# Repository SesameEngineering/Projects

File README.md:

# Projects
Current Sesame Projects

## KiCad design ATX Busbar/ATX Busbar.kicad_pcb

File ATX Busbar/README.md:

This project is a small PCb on which you plug a standard ATX PSU.

You can use it to power up OCP servers plugging it directly on the servers (Leopard V2, Tioga Pass and Yosemite V1) or using the busbar (Leopard V1, Bryce Canyon, Big Sur).

It can power up to 1kW.

It is also compatible with OCP Medusa cable to power up 3 servers at the same time.

On onboard LED indicates if power is on or not

Be careful when it is plugged not to touch directly the busbars. A plastic cover is used for safety

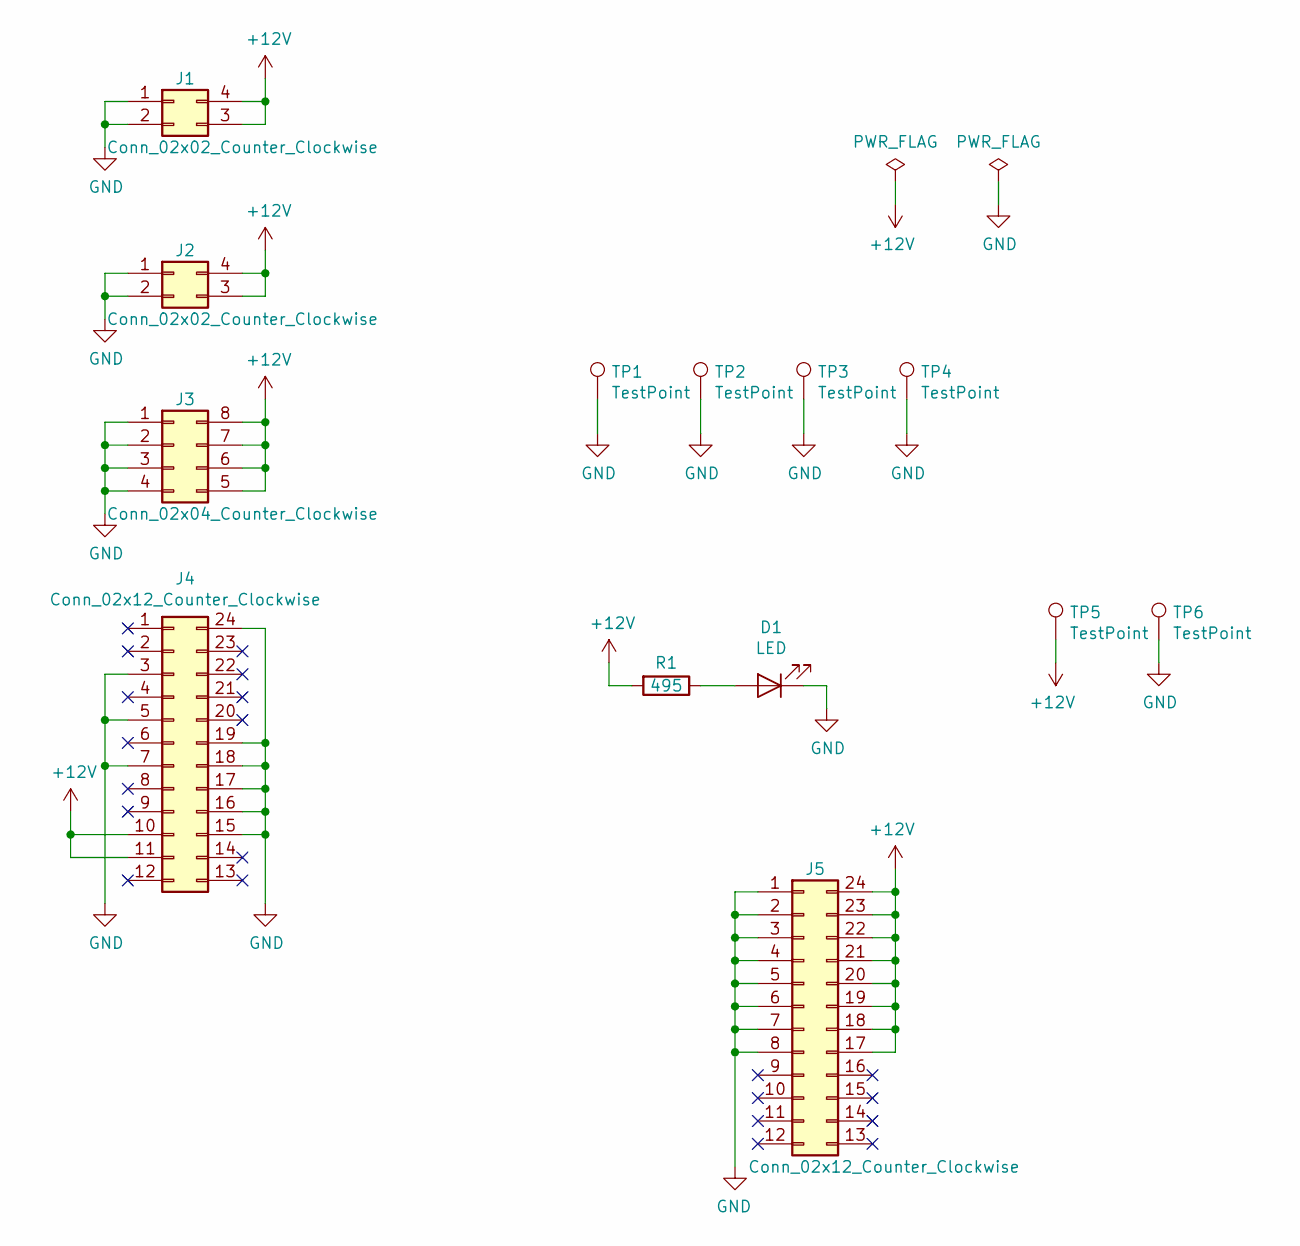
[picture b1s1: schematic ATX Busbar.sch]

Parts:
D1: LED; LED_1206
J1, J2: Conn_02x02_Counter_Clockwise; 2x2pins_2.38mm_0462070104
J3: Conn_02x04_Counter_Clockwise; 2x4pins_2.38mm_13A_0462070108
J4: Conn_02x12_Counter_Clockwise; Connector_2x12_2.5mm_thickness
J5: Conn_02x12_Counter_Clockwise; 2-6450880-8
R1: 495; R_1206
TP1, TP2, TP3, TP4: TestPoint; fixing_hole
TP5, TP6: TestPoint; pad_busbar

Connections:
+12V: J1.3, J1.4, J2.3, J2.4, J3.5, J3.6, J3.7, J3.8, J4.10, J4.11, J5.17, J5.18, J5.19, J5.20, J5.21, J5.22, J5.23, J5.24, R1.2, TP5.1
GND: D1.1 (K), J1.1, J1.2, J2.1, J2.2, J3.1, J3.2, J3.3, J3.4, J4.3, J4.5, J4.7, J4.15, J4.16, J4.17, J4.18, J4.19, J4.24, J5.1, J5.2, J5.3, J5.4, J5.5, J5.6, J5.7, J5.8, TP1.1, TP2.1, TP3.1, TP4.1, TP6.1
unnamed: D1.2 (A), R1.1

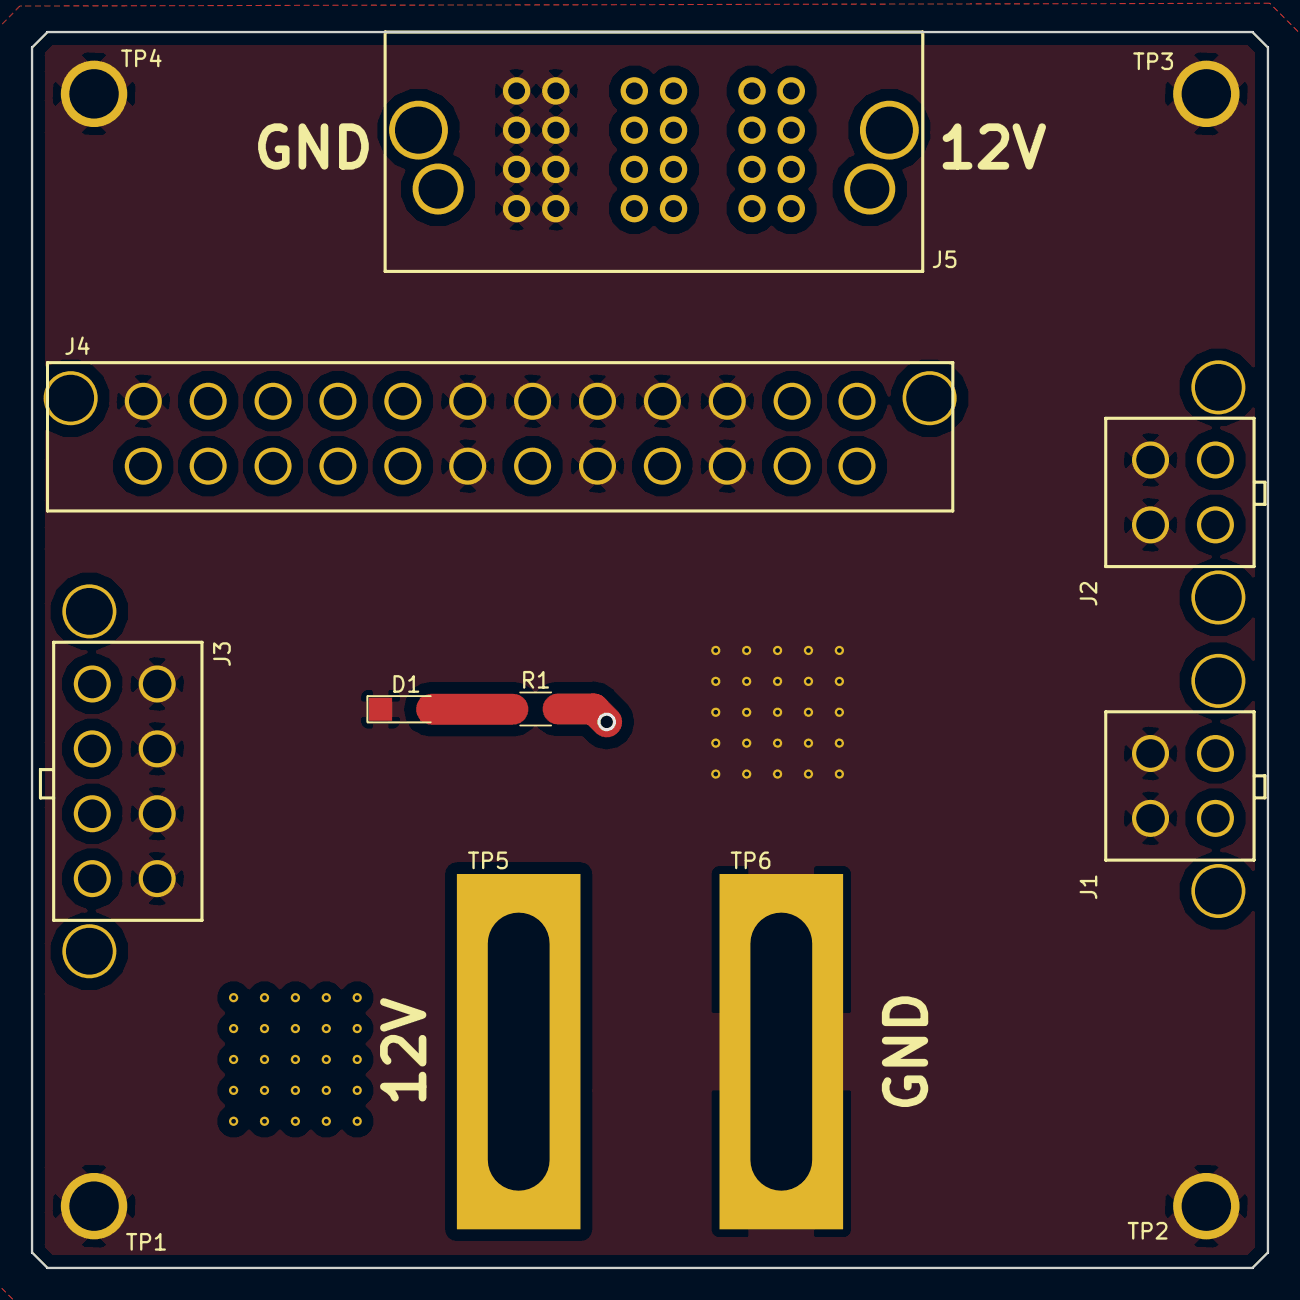
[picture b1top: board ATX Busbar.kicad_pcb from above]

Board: 2 copper layers, 80.0 x 80.0 mm, 13 parts (0 on the bottom side), 3 nets.

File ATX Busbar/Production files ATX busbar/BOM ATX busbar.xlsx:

Id | Reference | Footprint | Quantity | Designation | Manufacturer part number | Supplier part number | Manufacturer | Unit price | Total price | Comment
2 | D1 | LED_1206 | 1 | LED | 599-0260-007F | 645-599-0260-007F | Dialight | 0.34899999999999998 | 0.34899999999999998
3 | J1,J2 | power_SSD_2x2pins | 2 | Conn_02x02_Counter_Clockwise | 462070104 | WM20237-ND | Molex | 2.1800000000000002 | 4.3600000000000003
4 | J3 | proc_2x4pins | 1 | Conn_02x04_Counter_Clockwise | 462070108 | WM23313-ND | Molex | 2.62 | 2.62
5 | J4 | atx2x12pins | 1 | Conn_02x12_Counter_Clockwise | 46207-0124 | 538-46207-0124 | Molex | 5.67 | 5.67
6 | R1 | R_1206 | 1 | 495 | RT1206DRE07493RL | 603-RT1206DRE07493RL | Yageo | 0.46300000000000002 | 0.46300000000000002
7 | J5 | 2-6450880-8 | 1 | Conn_02x12_Counter_Clockwise |  |  |  |  |  | Pressfit - Provided by ITRenew - To assemble
 |  |  |  |  |  |  |  |  | 13.462

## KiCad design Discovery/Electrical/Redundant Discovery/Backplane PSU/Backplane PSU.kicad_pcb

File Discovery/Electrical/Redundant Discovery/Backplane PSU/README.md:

Design files and production files for the Backplane PSU (PCB on which you plug the PSUs)

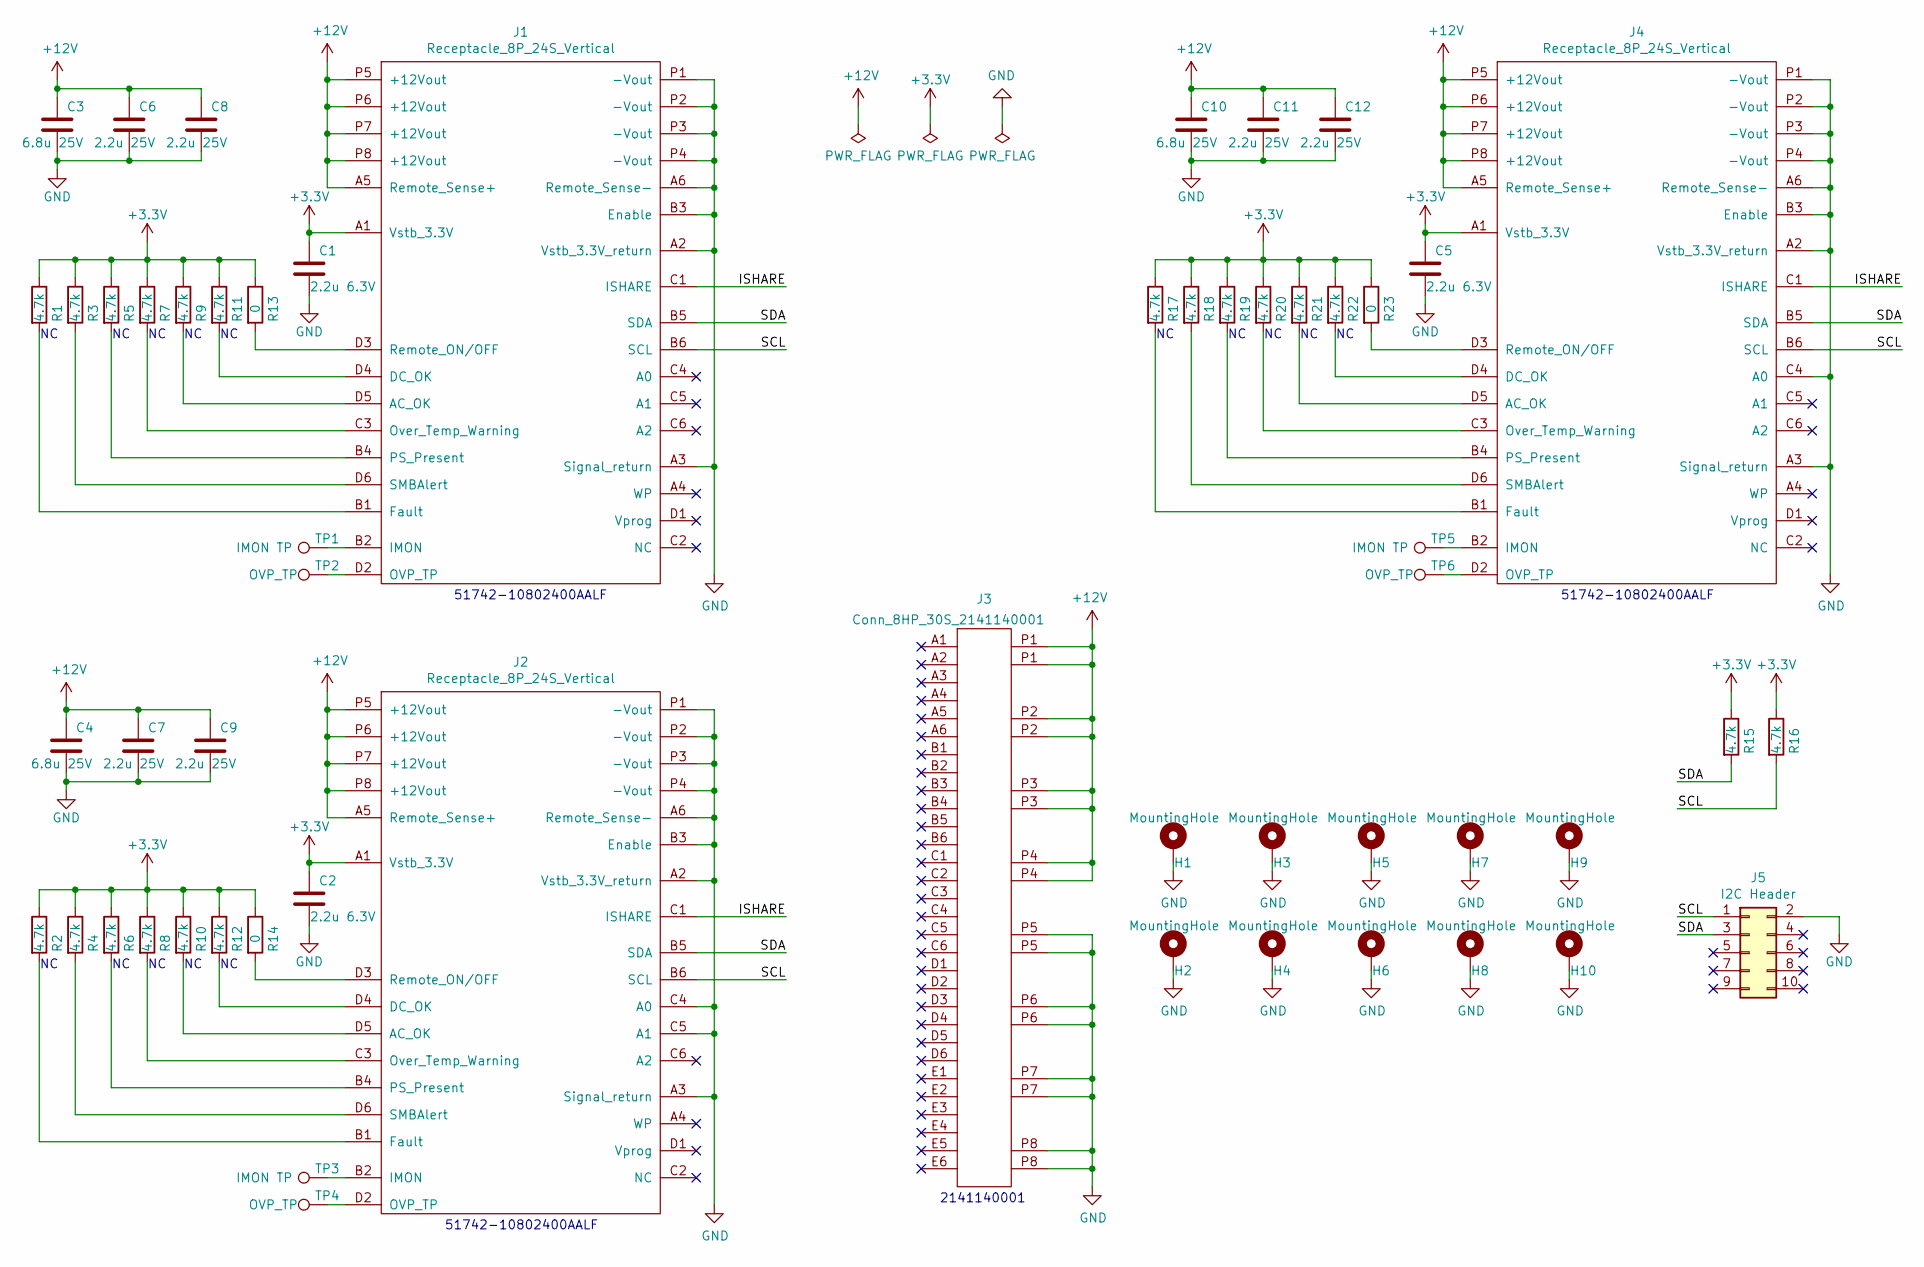
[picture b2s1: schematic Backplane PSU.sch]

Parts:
C1, C2, C5: 2.2u 6.3V; C_0805
C3, C4, C10: 6.8u 25V; C_0805
C6, C7, C8, C9, C11, C12: 2.2u 25V; C_0805
H1, H2, H3, H4, H5, H6, H7, H8, H9, H10: MountingHole; MountingHole_3.2mm_M3_Pad
J1, J2, J4: Receptacle_8P_24S_Vertical; PWR_Conn_8P+24S_51742-10802400AALF
J3: Conn_8HP_30S_2141140001
J5: I2C Header; Pin_Header_Straight_2x05_Pitch2.54mm
R1, R2, R3, R4, R5, R6, R7, R8, R9, R10, R11, R12, R15, R16, R17, R18, R19, R20, R21, R22: 4.7k; R_0805
R13, R14, R23: 0; R_0805
TP1, TP3, TP5: IMON TP; TestPoint_Pad_D1.5mm
TP2, TP4, TP6: OVP_TP; TestPoint_Pad_D1.5mm

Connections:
+3V3: C1.1, C2.1, C5.1, J1.A1 (Vstb_3.3V), J2.A1 (Vstb_3.3V), J4.A1 (Vstb_3.3V), R1.1, R2.1, R3.1, R4.1, R5.1, R6.1, R7.1, R8.1, R9.1, R10.1, R11.1, R12.1, R13.1, R14.1, R15.1, R16.1, R17.1, R18.1, R19.1, R20.1, R21.1, R22.1, R23.1
+12V: C3.1, C4.1, C6.1, C7.1, C8.1, C9.1, C10.1, C11.1, C12.1, J1.A5 (Remote_Sense+), J1.P5 (+12Vout), J1.P6 (+12Vout), J1.P7 (+12Vout), J1.P8 (+12Vout), J2.A5 (Remote_Sense+), J2.P5 (+12Vout), J2.P6 (+12Vout), J2.P7 (+12Vout), J2.P8 (+12Vout), J3.P1, J3.P2, J3.P3, J3.P4, J4.A5 (Remote_Sense+), J4.P5 (+12Vout), J4.P6 (+12Vout), J4.P7 (+12Vout), J4.P8 (+12Vout)
/ISHARE: J1.C1 (ISHARE), J2.C1 (ISHARE), J4.C1 (ISHARE)
/SCL: J1.B6 (SCL), J2.B6 (SCL), J4.B6 (SCL), J5.1, R16.2
/SDA: J1.B5 (SDA), J2.B5 (SDA), J4.B5 (SDA), J5.3, R15.2
GND: C1.2, C2.2, C3.2, C4.2, C5.2, C6.2, C7.2, C8.2, C9.2, C10.2, C11.2, C12.2, H1.1, H2.1, H3.1, H4.1, H5.1, H6.1, H7.1, H8.1, H9.1, H10.1, J1.A2 (Vstb_3.3V_return), J1.A3 (Signal_return), J1.A6 (Remote_Sense-), J1.B3 (Enable), J1.P1 (-Vout), J1.P2 (-Vout), J1.P3 (-Vout), J1.P4 (-Vout), J2.A2 (Vstb_3.3V_return), J2.A3 (Signal_return), J2.A6 (Remote_Sense-), J2.B3 (Enable), J2.C4 (A0), J2.C5 (A1), J2.P1 (-Vout), J2.P2 (-Vout), J2.P3 (-Vout), J2.P4 (-Vout), J3.P5, J3.P6, J3.P7, J3.P8, J4.A2 (Vstb_3.3V_return), J4.A3 (Signal_return), J4.A6 (Remote_Sense-), J4.B3 (Enable), J4.C4 (A0), J4.P1 (-Vout), J4.P2 (-Vout), J4.P3 (-Vout), J4.P4 (-Vout), J5.2
unnamed: J1.B1 (Fault), R1.2
unnamed: J1.B2 (IMON), TP1.1
unnamed: J1.B4 (PS_Present), R5.2
unnamed: J1.C3 (Over_Temp_Warning), R7.2
unnamed: J1.D2 (OVP_TP), TP2.1
unnamed: J1.D3 (Remote_ON/OFF), R13.2
unnamed: J1.D4 (DC_OK), R11.2
unnamed: J1.D5 (AC_OK), R9.2
unnamed: J1.D6 (SMBAlert), R3.2
unnamed: J2.B1 (Fault), R2.2
unnamed: J2.B2 (IMON), TP3.1
unnamed: J2.B4 (PS_Present), R6.2
unnamed: J2.C3 (Over_Temp_Warning), R8.2
unnamed: J2.D2 (OVP_TP), TP4.1
unnamed: J2.D3 (Remote_ON/OFF), R14.2
unnamed: J2.D4 (DC_OK), R12.2
unnamed: J2.D5 (AC_OK), R10.2
unnamed: J2.D6 (SMBAlert), R4.2
unnamed: J4.B1 (Fault), R17.2
unnamed: J4.B2 (IMON), TP5.1
unnamed: J4.B4 (PS_Present), R19.2
unnamed: J4.C3 (Over_Temp_Warning), R20.2
unnamed: J4.D2 (OVP_TP), TP6.1
unnamed: J4.D3 (Remote_ON/OFF), R23.2
unnamed: J4.D4 (DC_OK), R22.2
unnamed: J4.D5 (AC_OK), R21.2
unnamed: J4.D6 (SMBAlert), R18.2

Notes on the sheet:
51742-10802400AALF
2141140001

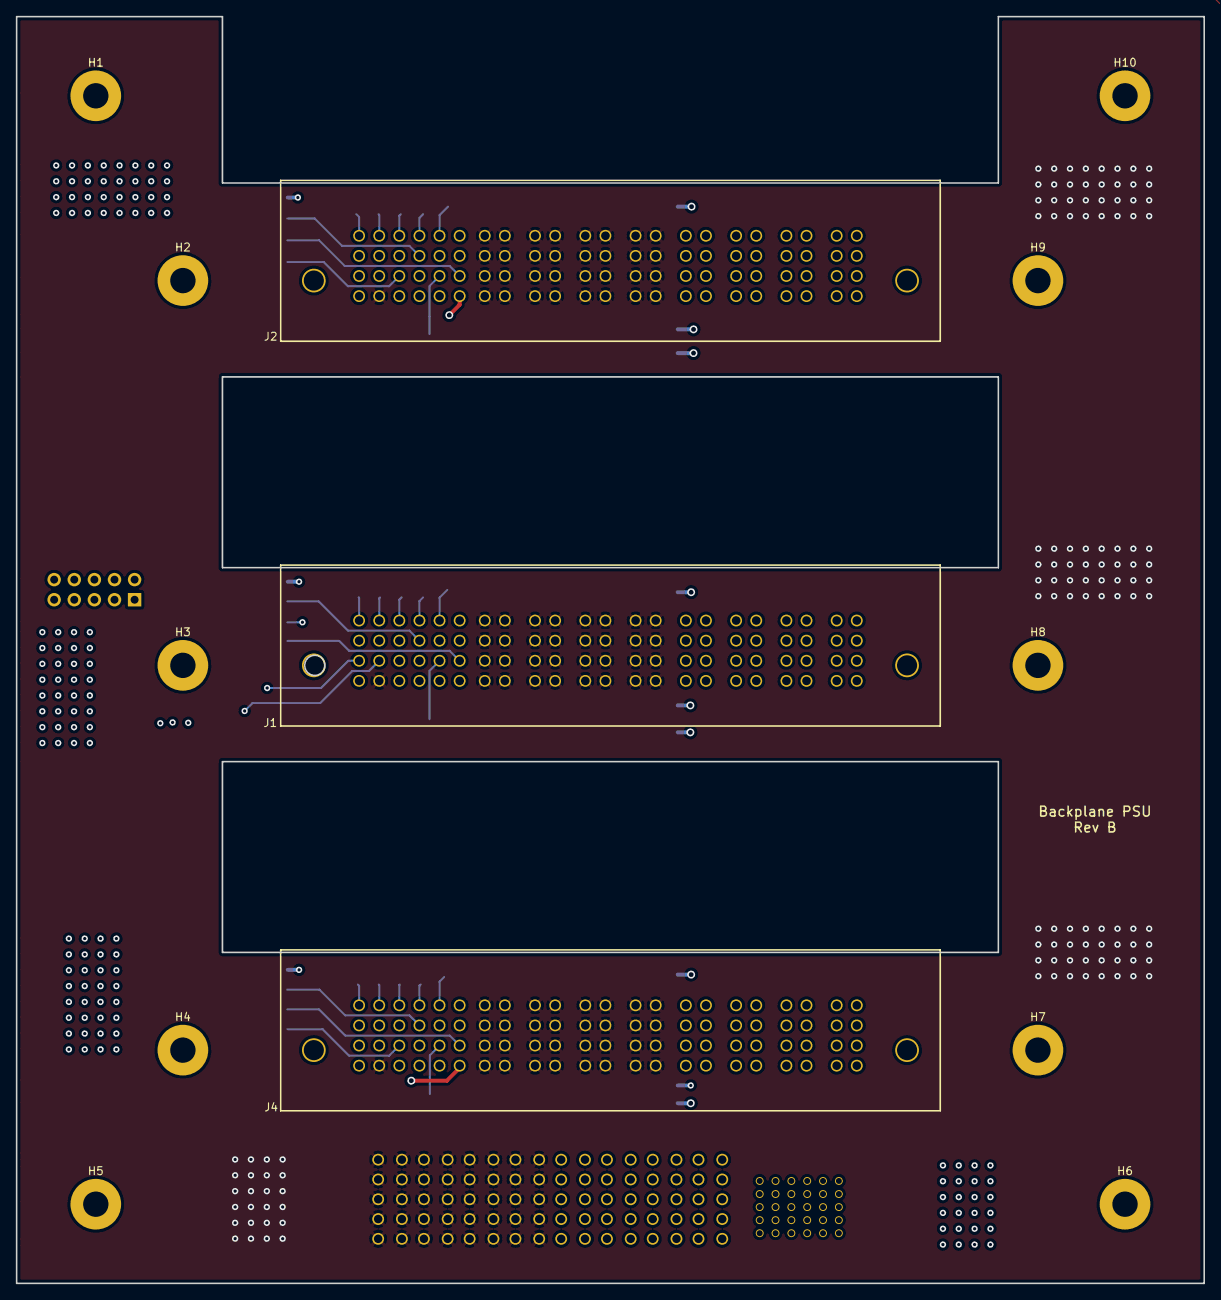
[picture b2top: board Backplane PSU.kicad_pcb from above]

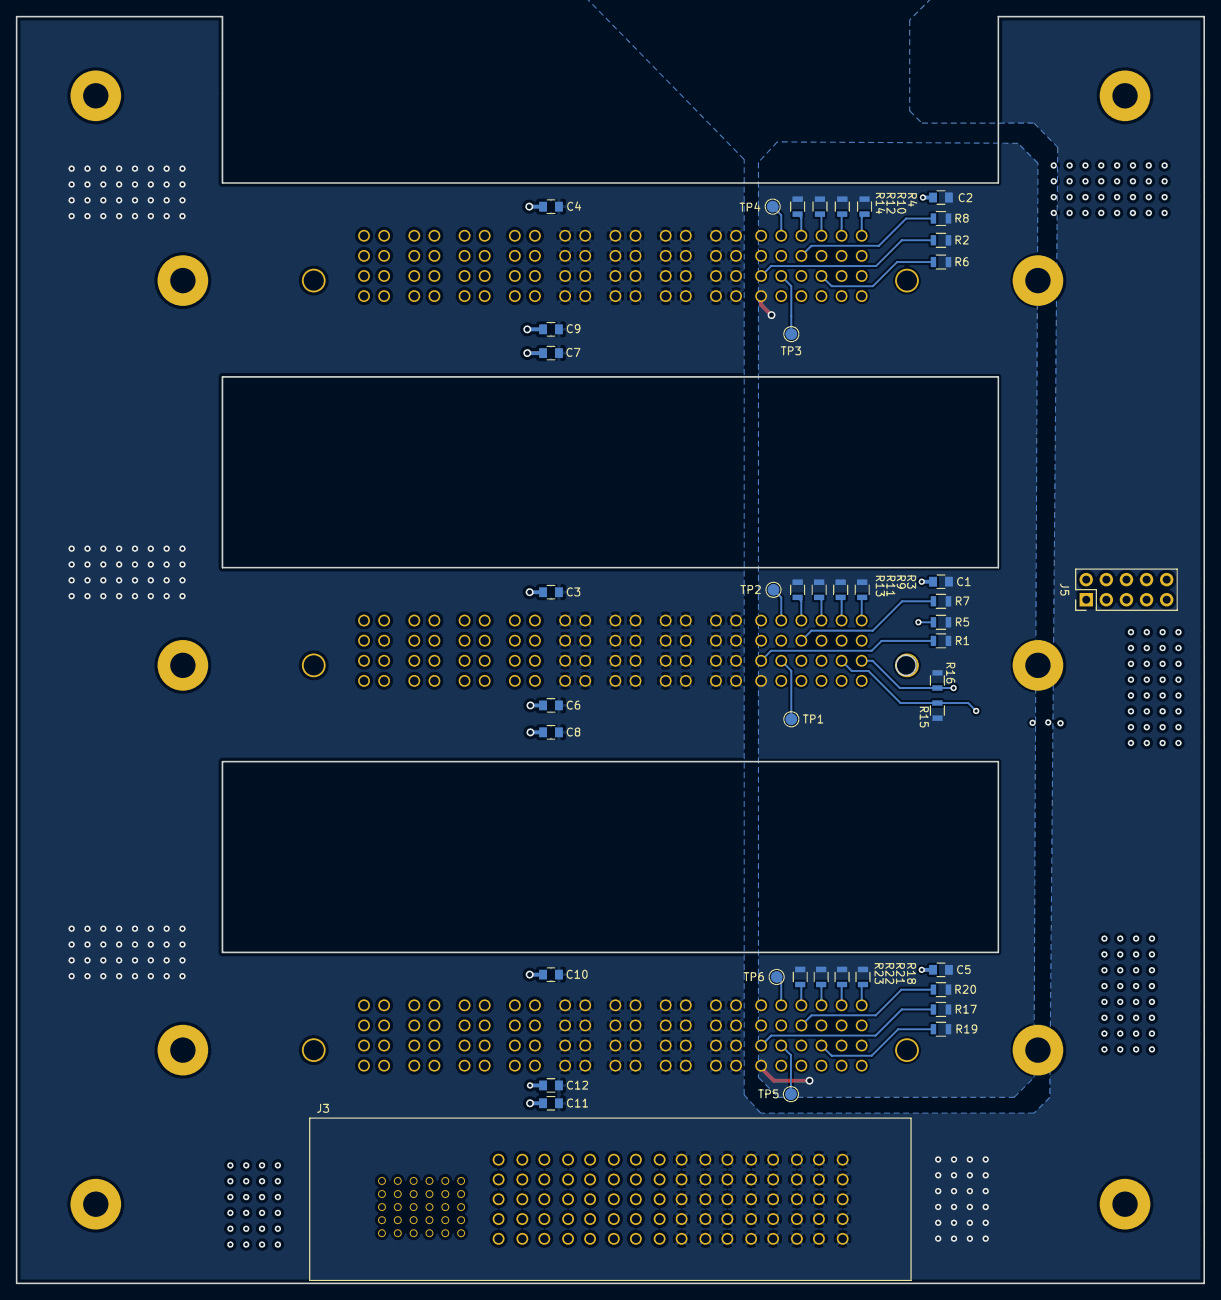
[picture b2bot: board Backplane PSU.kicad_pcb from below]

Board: 4 copper layers, 150.0 x 160.0 mm, 56 parts (43 on the bottom side), 33 nets.

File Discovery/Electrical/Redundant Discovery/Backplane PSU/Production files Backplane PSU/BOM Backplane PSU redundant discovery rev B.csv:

Id;Reference;Footprint;Quantity;Designation;Manufacturer part number;Manufacturer;Comments
1;C1,C2,C5;C_0805;3;2.2u 6.3V;08056C225KAT2A;AVX;
2;R1,R2,R3,R4,R5,R6,R7,R8,R9,R10,R11,R12,R15,R16,R17,R18,R19,R20,R21,R22;R_0805;20;4.7k;CRCW08054K70JNEA;Vishay / Dale;
3;R13,R14,R23;R_0805;3;0;CR0805AJ/-000EAS;Bourns;
6;J3;Conn_8HP_30S_2141140001;1;Conn_8HP_30S_2141140001;2141140001;Molex;
8;J5;Pin_Header_Straight_2x05_Pitch2.54mm;1;I2C Header;67996-410-060024LF;Amphenol FCI;
9;C3,C4,C10;C_0805;3;6.8u 25V;C2012X5R1E685K125AC;TDK ;
10;C6,C7,C8,C9,C11,C12;C_0805;6;2.2u 25V;C0805X225K3RACAUTO;KEMET;
11;J4,J1,J2;PWR_Conn_8P+24S_51742-10802400AALF;3;Receptacle_8P_24S_Vertical;51742-10802400AALF;Amphenol FCI;

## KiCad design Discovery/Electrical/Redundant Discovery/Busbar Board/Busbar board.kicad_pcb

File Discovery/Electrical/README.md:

This folder contains all of the electrical files for both standard Discovery and redundant Discovery.

For each, you have the design file (Kicad) and the production files (it includes the PCB, the set of mini Busbar and cables)

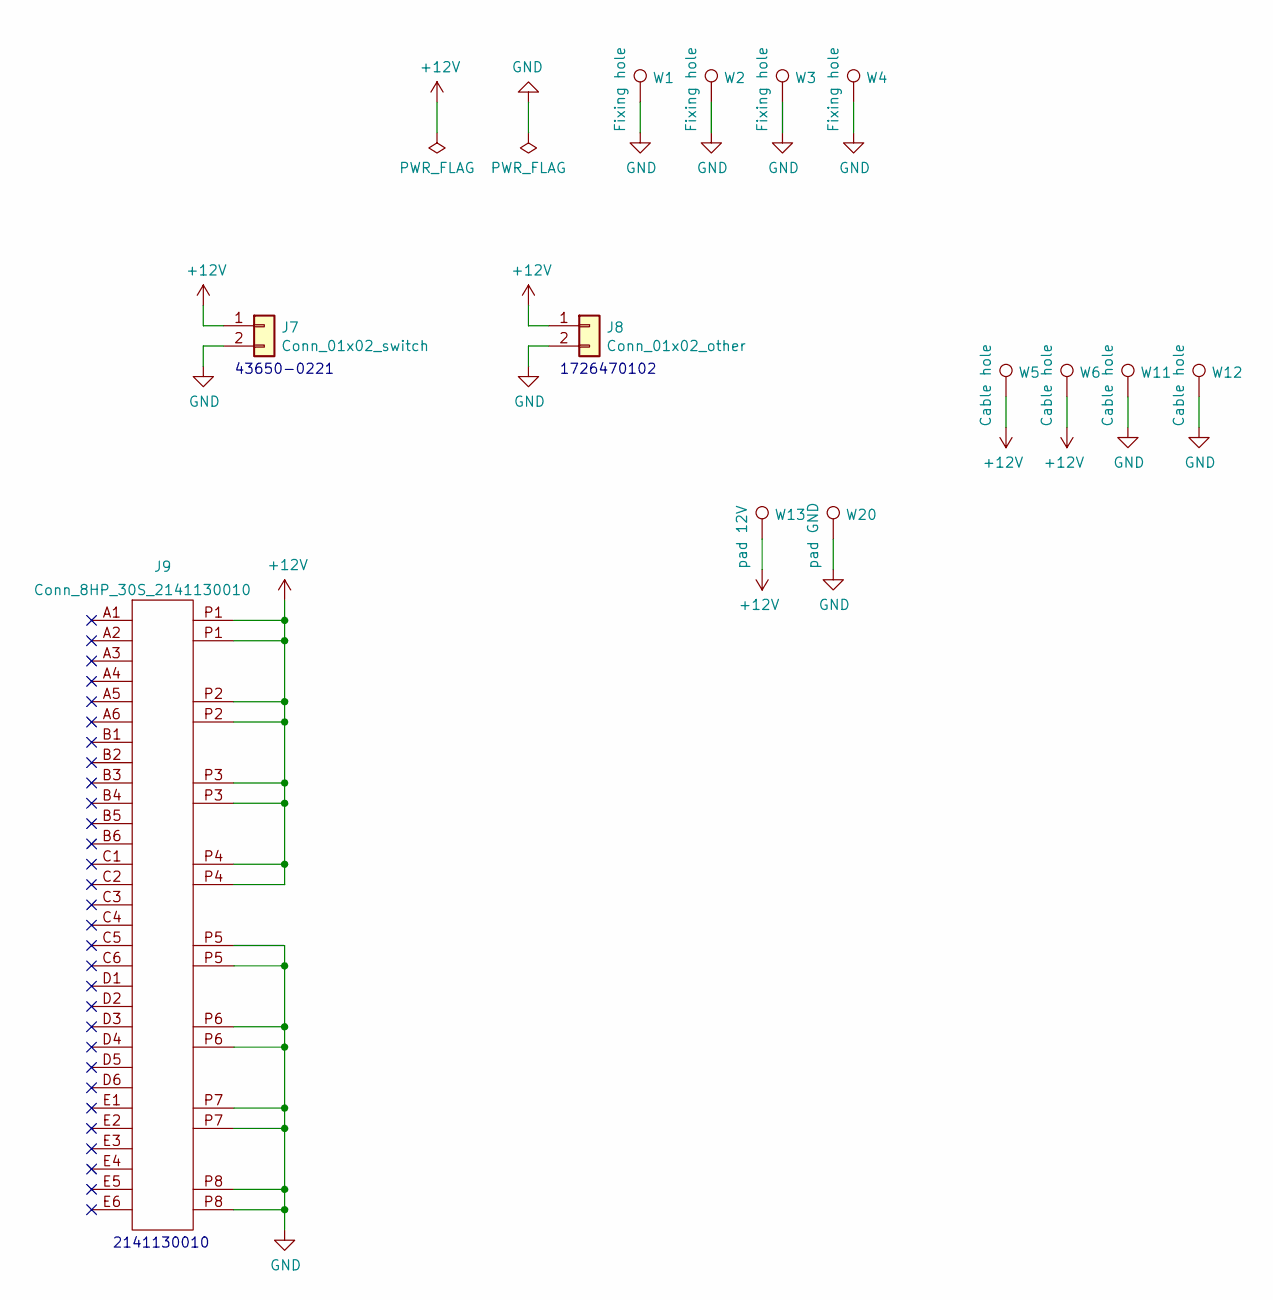
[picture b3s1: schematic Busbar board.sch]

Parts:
J7: Conn_01x02_switch; 2pins_2.54mm_43650-0221
J8: Conn_01x02_other; Conn_01x02_straight_4.2mm_9A_1726470102
J9: Conn_8HP_30S_2141130010; Conn_8HP_30S_RA_2141130010
W1, W2, W3, W4: Fixing hole; FixingPoint_Plated_Hole_D4.0mm
W5, W6, W11, W12: Cable hole; fixing_hole
W13: pad 12V; pad_high_power
W20: pad GND; pad_high_power

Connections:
+12V: J7.1, J8.1, J9.P1, J9.P2, J9.P3, J9.P4, W5.1, W6.1, W13.1
GND: J7.2, J8.2, J9.P5, J9.P6, J9.P7, J9.P8, W1.1, W2.1, W3.1, W4.1, W11.1, W12.1, W20.1

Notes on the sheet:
43650-0221
1726470102
2141130010

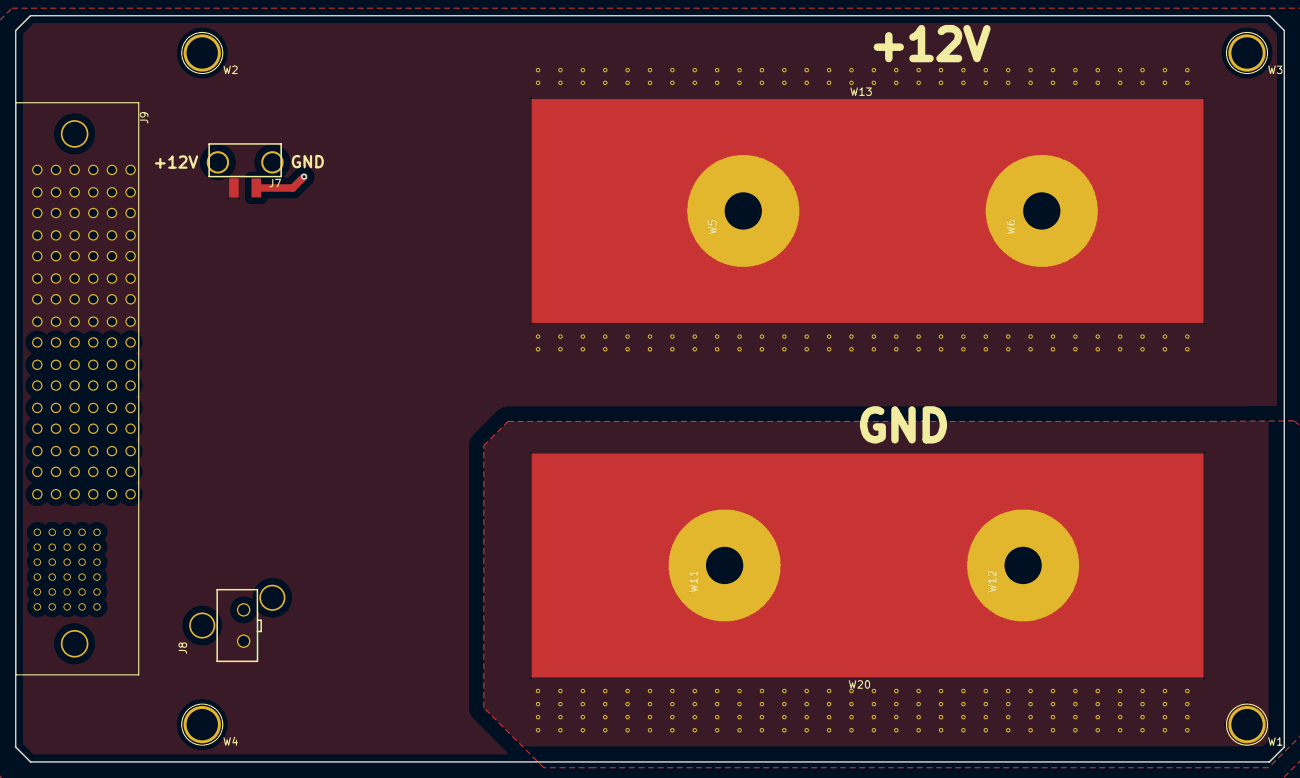
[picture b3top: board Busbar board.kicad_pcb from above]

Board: 2 copper layers, 170.0 x 100.0 mm, 13 parts (0 on the bottom side), 2 nets.

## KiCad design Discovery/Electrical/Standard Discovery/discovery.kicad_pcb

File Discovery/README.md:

THIS FOLDER CONTAINS ALL SPECIFICATIONS DOCUMENTATION, MANUFACTURING DRAWINGS AND CAD FOR THE DISCOVERY

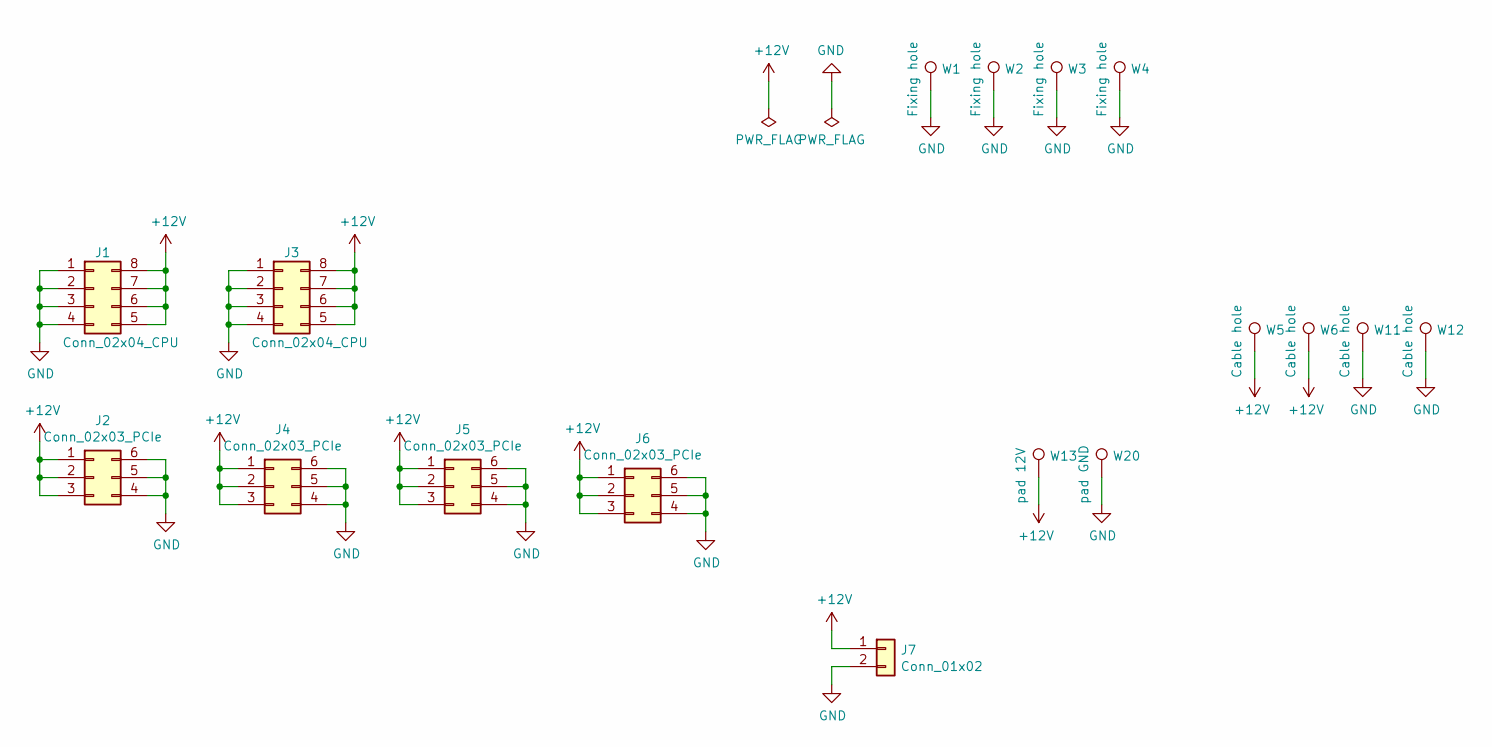
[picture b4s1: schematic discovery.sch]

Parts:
J1, J3: Conn_02x04_CPU; CONN_02x04_4.2mm
J2, J4, J5, J6: Conn_02x03_PCIe; CONN_02x03_4.2mm
J7: Conn_01x02; 2pins_2.54mm_43650-0221
W1, W2, W3, W4: Fixing hole; FixingPoint_Plated_Hole_D4.0mm
W5, W6, W11, W12: Cable hole; fixing_hole
W13: pad 12V; pad_high_power
W20: pad GND; pad_high_power

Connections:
+12V: J1.5, J1.6, J1.7, J1.8, J2.1, J2.2, J2.3, J3.5, J3.6, J3.7, J3.8, J4.1, J4.2, J4.3, J5.1, J5.2, J5.3, J6.1, J6.2, J6.3, J7.1, W5.1, W6.1, W13.1
GND: J1.1, J1.2, J1.3, J1.4, J2.4, J2.5, J2.6, J3.1, J3.2, J3.3, J3.4, J4.4, J4.5, J4.6, J5.4, J5.5, J5.6, J6.4, J6.5, J6.6, J7.2, W1.1, W2.1, W3.1, W4.1, W11.1, W12.1, W20.1

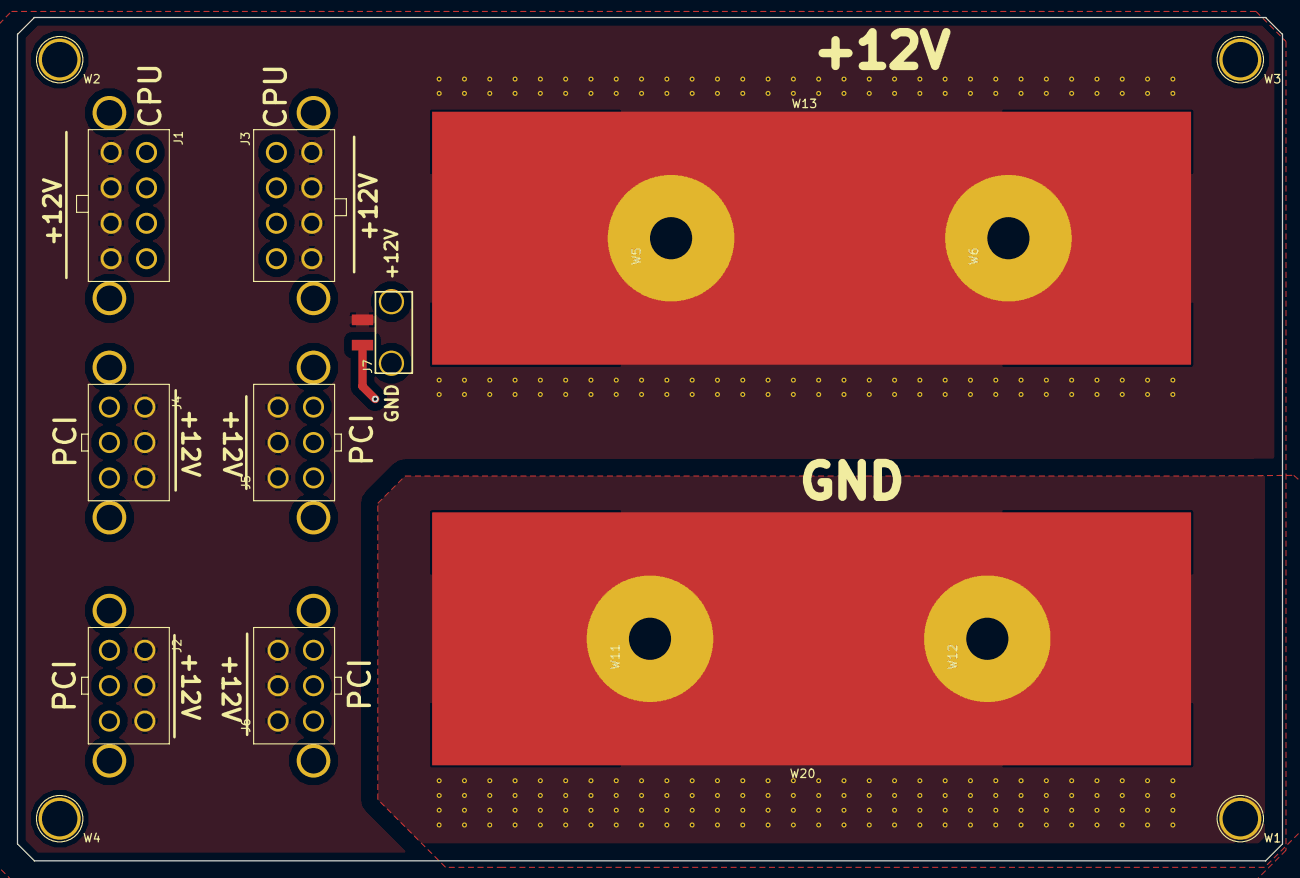
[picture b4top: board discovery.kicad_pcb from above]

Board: 2 copper layers, 150.0 x 100.0 mm, 17 parts (0 on the bottom side), 2 nets.
